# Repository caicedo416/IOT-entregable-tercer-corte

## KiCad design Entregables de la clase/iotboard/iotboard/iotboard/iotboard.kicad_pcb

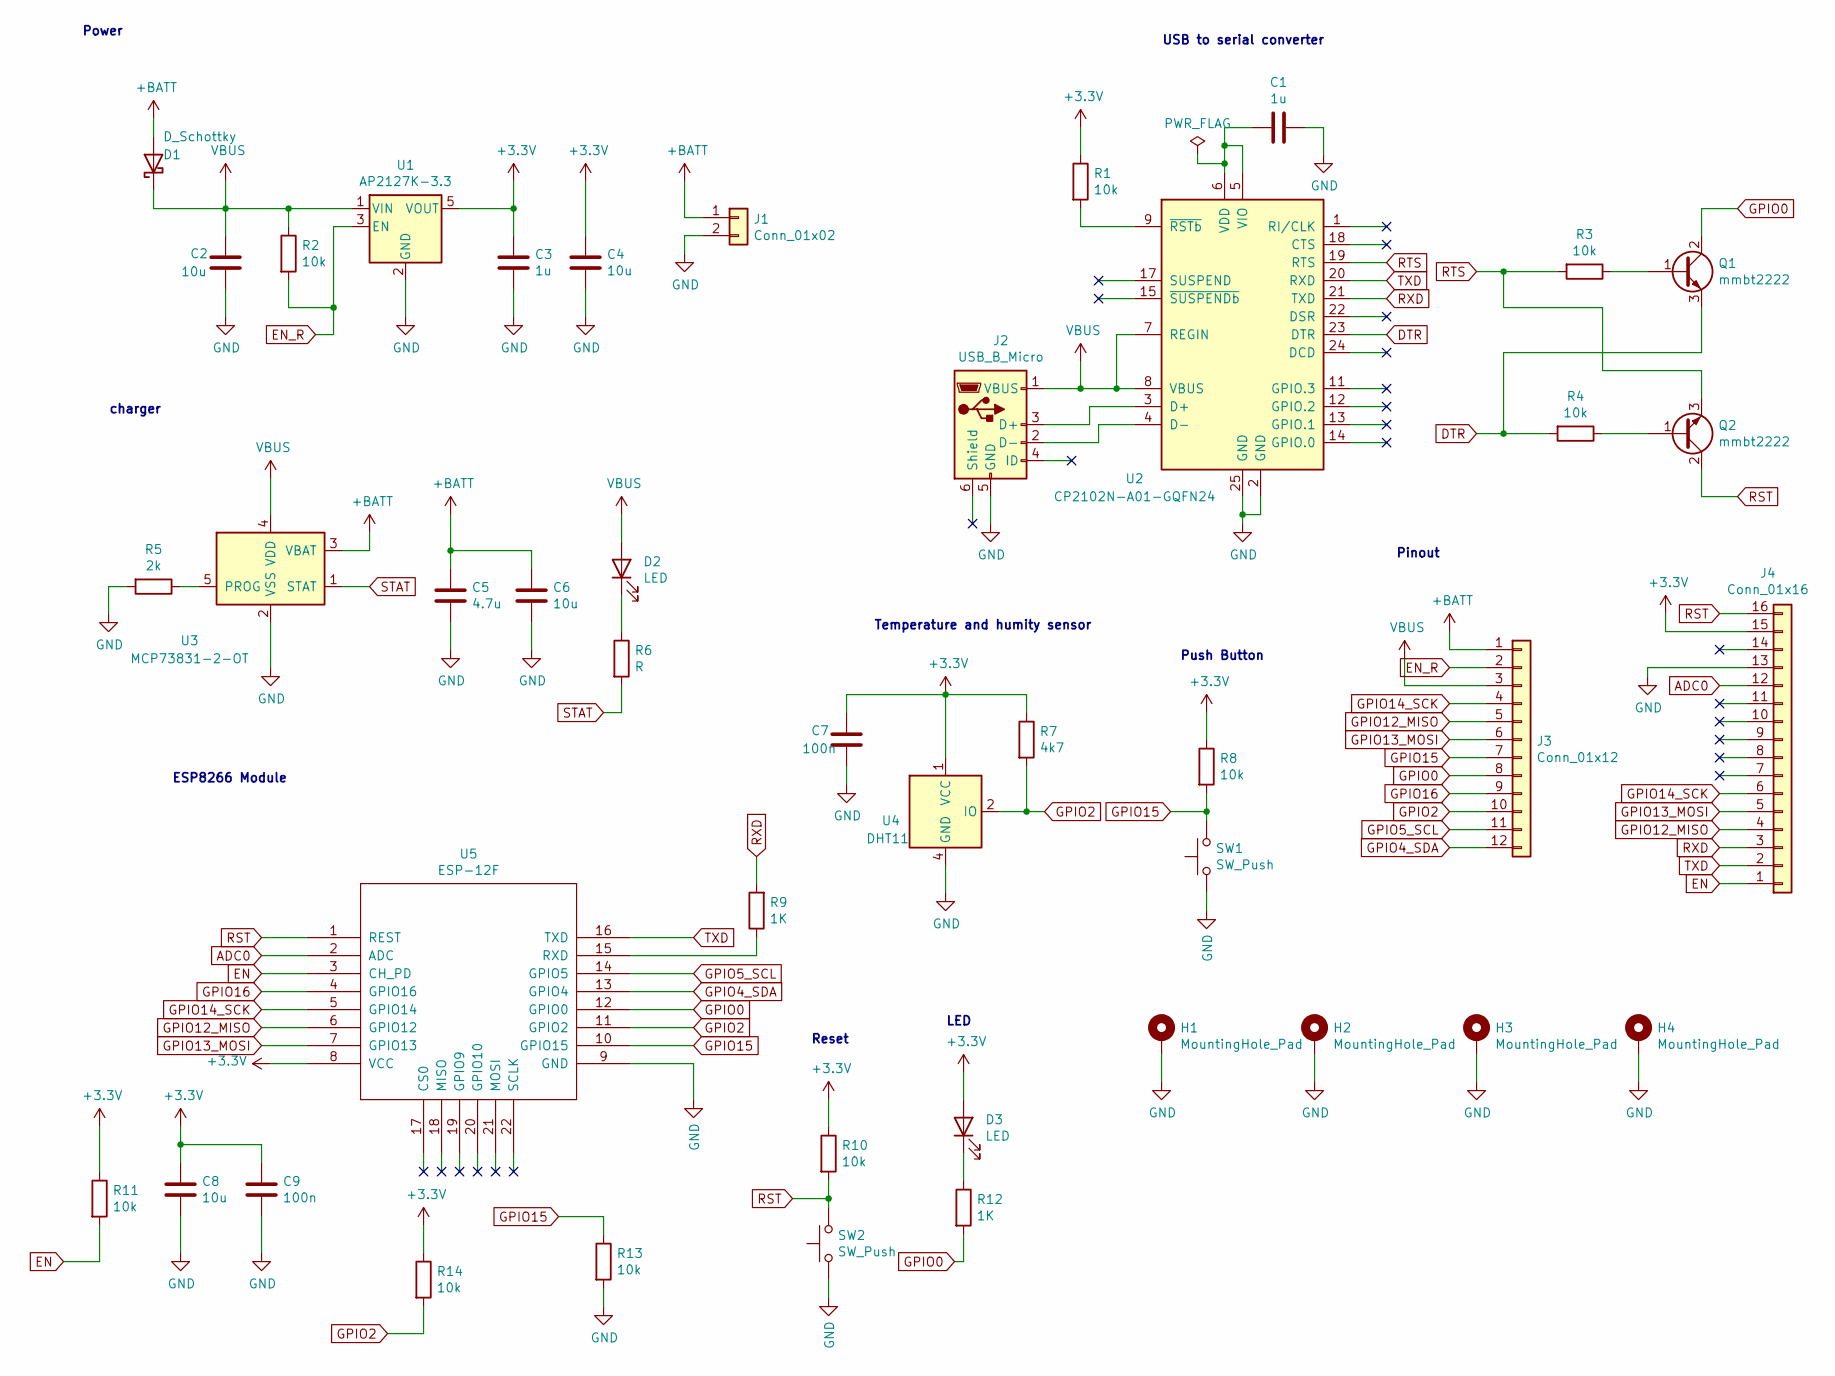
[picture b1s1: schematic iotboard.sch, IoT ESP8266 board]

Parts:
C1, C3: 1u; C_0603_1608Metric_Pad1.08x0.95mm_HandSolder
C2, C4, C6, C8: 10u; C_0603_1608Metric_Pad1.08x0.95mm_HandSolder
C5: 4.7u; C_0603_1608Metric_Pad1.08x0.95mm_HandSolder
C7, C9: 100n; C_0603_1608Metric_Pad1.08x0.95mm_HandSolder
D1: D_Schottky; D_0603_1608Metric_Pad1.05x0.95mm_HandSolder
D2, D3: LED; LED_0805_2012Metric_Pad1.15x1.40mm_HandSolder
H1, H2, H3, H4: MountingHole_Pad; MountingHole_3mm_Pad_Via
J1: Conn_01x02; JST_XH_S2B-XH-A_1x02_P2.50mm_Horizontal
J2: USB_B_Micro; USB_Micro-B_Molex_47346-0001
J3: Conn_01x12; PinSocket_1x12_P2.54mm_Vertical
J4: Conn_01x16; PinSocket_1x16_P2.54mm_Vertical
Q1, Q2: mmbt2222; SOT-23
R1, R2, R3, R4, R8, R10, R11, R13, R14: 10k; R_0603_1608Metric_Pad0.98x0.95mm_HandSolder
R5: 2k; R_0603_1608Metric_Pad0.98x0.95mm_HandSolder
R6: R; R_0603_1608Metric_Pad0.98x0.95mm_HandSolder
R7: 4k7; R_0603_1608Metric_Pad0.98x0.95mm_HandSolder
R9, R12: 1K; R_0603_1608Metric_Pad0.98x0.95mm_HandSolder
SW1, SW2: SW_Push; SW_SPST_EVPBF
U1: AP2127K-3.3; SOT-23-5
U2: CP2102N-A01-GQFN24; QFN-24-1EP_4x4mm_P0.5mm_EP2.6x2.6mm
U3: MCP73831-2-OT; SOT-23-5
U4: DHT11; Aosong_DHT11_5.5x12.0_P2.54mm
U5: ESP-12F; ESP-12E

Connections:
+3V3: C3.1, C4.1, C7.1, C8.1, C9.1, D3.2 (A), J4.15, R1.1, R7.1, R8.1, R10.1, R11.1, R14.1, U1.5 (VOUT), U4.1 (VCC), U5.8 (VCC)
+BATT: C5.1, C6.1, D1.2 (A), J1.1, J3.1, U3.3 (VBAT)
ADC0: J4.12, U5.2 (ADC)
DTR: Q1.3 (E), R4.2, U2.23 (DTR)
EN: J4.1, R11.2, U5.3 (CH_PD)
EN_R: J3.2, R2.2, U1.3 (EN)
GND: C1.1, C2.2, C3.2, C4.2, C5.2, C6.2, C7.2, C8.2, C9.2, H1.1, H2.1, H3.1, H4.1, J1.2, J2.5 (GND), J4.13, R5.2, R13.2, SW1.1, SW2.1, U1.2 (GND), U2.2 (GND), U2.25 (GND), U3.2 (VSS), U4.4 (GND), U5.9 (GND)
GPIO0: J3.8, Q1.2 (C), R12.2, U5.12 (GPIO0)
GPIO2: J3.10, R7.2, R14.2, U4.2 (IO), U5.11 (GPIO2)
GPIO4_SDA: J3.12, U5.13 (GPIO4)
GPIO5_SCL: J3.11, U5.14 (GPIO5)
GPIO12_MISO: J3.5, J4.4, U5.6 (GPIO12)
GPIO13_MOSI: J3.6, J4.5, U5.7 (GPIO13)
GPIO14_SCK: J3.4, J4.6, U5.5 (GPIO14)
GPIO15: J3.7, R8.2, R13.1, SW1.2, U5.10 (GPIO15)
GPIO16: J3.9, U5.4 (GPIO16)
unnamed: C1.2, U2.5 (VIO), U2.6 (VDD)
unnamed: D2.1 (K), R6.1
unnamed: D3.1 (K), R12.1
unnamed: J2.2 (D-), U2.4 (D-)
unnamed: J2.3 (D+), U2.3 (D+)
unnamed: Q1.1 (B), R3.1
unnamed: Q2.1 (B), R4.1
unnamed: R1.2, U2.9 (~RSTb)
unnamed: R5.1, U3.5 (PROG)
unnamed: R9.1, U5.15 (RXD)
RST: J4.16, Q2.2 (C), R10.2, SW2.2, U5.1 (REST)
RTS: Q2.3 (E), R3.2, U2.19 (RTS)
RXD: J4.3, R9.2, U2.21 (TXD)
STAT: R6.2, U3.1 (STAT)
TXD: J4.2, U2.20 (RXD), U5.16 (TXD)
VBUS: C2.1, D1.1 (K), D2.2 (A), J2.1 (VBUS), J3.3, R2.1, U1.1 (VIN), U2.7 (REGIN), U2.8 (VBUS), U3.4 (VDD)

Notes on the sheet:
ESP8266 Module
LED
Power
Temperature and humity sensor
Reset
charger
USB to serial converter
Push Button
Pinout

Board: 2 copper layers, 43 parts (0 on the bottom side), 32 nets, no tracks yet.

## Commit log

2020-12-08 caicedo1221
